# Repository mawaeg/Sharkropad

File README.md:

# Sharkropad

**Sharkropad** is an open-source hotswappable macropad supporting QMK/VIA.

This repository includes a custom pcb design, a 3d printed case and QMK/VIA firmware.

## Features
- **USB-C with ESD Protection**
- **Rotary Encoder**
- **OLED Display**
- **Customizable RGB Lighting**
- **Customizable keymap using VIA**
- **Hot-Swappable Switches**
- **Powered by a STM32L432 MCU**

## Getting Started

### Pcb

The Sharkropad is based on a custom pcb. You can find the manufacturing files in the latest release.

I got my pcb manufactured and assembled from [JLCPCB](https://jlcpcb.com/).

In case you want to assemble the pcb yourself you can find all the needed parts in the bom in the latest release.

### Other needed parts

| Part                      | Quantity  | Link (recommendation) | Note |
|---------------------------|-----------|-----------------------|------|
| filament of your choice   | 50g       | [3djake.de](https://www.3djake.de/polymaker/polyterra-pla-charcoal-black)                   | For the top parts (I used a matte black PLA filament)
| transparent filament      | 30g       | [redline-filament.com](https://redline-filament.com/collections/pla-filament/products/premium-pla-transparent?variant=50149105041672)                  | Transparent bottom parts for the underglow
| M2.5 Heat Inserts         | 4         | [cnckitchen.store](https://cnckitchen.store/products/gewindeeinsatz-threaded-insert-m2-5-standard-100-stk-pcs)                   |
| M2.5 x 12 Screws          | 4         | [cnckitchen.store](https://cnckitchen.store/products/m2-5-screw-stainless-steel-aisi-304-low-head?variant=47945362833743)                  |
| Protective buffer         | 4         | [amazon.de](https://www.amazon.de/dp/B01N0X4Y38?ref=ppx_yo2ov_dt_b_fed_asin_title&th=1) |
| Keycaps                   | 12        | [aliexpress.com](https://de.aliexpress.com/item/1005006660909685.html?spm=a2g0o.order_list.order_list_main.15.49fc5c5fYY4A21&gatewayAdapt=glo2deu)
| Stranded wire             | 10cm      | tbd | Currently there is a problem with the pcb when using the underglow leds where a cable needs to be soldered
| Rotary Encoder            | 1         | [42keebs.eu](https://42keebs.eu/shop/parts/ec11-rotary-encoder/?attribute_type=Bourns%20(larger%20body)) | This particular one works with the case and the knob
| OLED display              | 1         | [42keebs.eu](https://42keebs.eu/shop/parts/oled-display-0-91-128x32/?attribute_pcb-colour=Black)
| OLED socket (low profile) | 1         | [42keebs.eu](https://42keebs.eu/shop/parts/low-profile-oled-sockets/) 
| Hotswap sockets           | 12        | [42keebs.eu](https://42keebs.eu/shop/parts/kailh-mx-hot-swap-sockets/) | (2 x 10 sockets) !Cherry MX-style!
| Switches                  | 12        | [candykeys.com](https://candykeys.com/product/hmx-silent-sakura) | Any MX compatible switch is fine

### 3d printed case

The case consists of 4 3d printed parts:
- Bottom part of the case
- Top part of the case
- Plate for the switches
- Rotary encoder knob

The stl files for the 3d printed parts can be found under [cad/stl/](cad/stl/).

The parts are created with [OpenSCAD](https://openscad.org/) and the source code is stored at [cad/](cad/).

#### Print settings

For the bottom part of the case I used transparent PLA to make the underglow leds shine through.

For the top part of the case, the plate and the rotary encoder knob I used matte black PLA.

I printed the case and the plate with default print settings with a layer height of .2mm.

> **_NOTE:_** For the top and bottom case you will need some supports for the cutouts for the encoder and the screw heads. Default support settings should work just fine. (I like to use organic supports.)

The rotary encoder knob should be printed with a layer height of .2mm and at least 3 solid bottom layers.

### Building the Sharkropad

1. Get a PCB and prepare it by soldering the components onto it (if not already done through SMT assembly)
2. Assemble the rotary encoder, the oled socket and the hotswap sockets (if not already done)
3. Fix the issue with the pcb as shown in [this chapter](#fixing-the-pcb)

    <div style="display: flex;">

    </div>

4. Place a foam (as shown) to support the OLED and mount the oled:

5. Assemble the switches (put the plate between pcb and switches) and the keycaps
6. Insert the heat inserts into the holes provided in the top part:

7. Put the protective buffers on the bottom case to prevent the macropad from sliding around:

8. Screw the case together with the pcb in between and put the knob on the rotary encoder

### Flashing the firmware

> **_NOTE:_** Once the firmware is flashed once you can enter bootloader mode by disconnecting the macropad, pressing and holding the encoder knob while plugging it back in. Then the macropad is in bootloader mode and you can connect to it  and program it using the CubeProgrammer or flash using QMK.

1. Get the provided firmware in the latest release
    - If you want to be able to use VIA to modify the keymap you should use `sharkropad_via.bin`
    - If you only need QMK functionality you can also use ` sharkropad_default.bin`
    
2. Flash the firmware using the [STM32 CubeProgrammer](https://www.st.com/en/development-tools/stm32cubeprog.html) as shown below:

#### Flash using QMK

As the firmware is not currently in the qmk github repository flashing with QMK is more complicated.
- You need to setup your QMK Environment
- Copy the firmware into the QMK folder:
    - Copy the contents of the firmware folder to a folder named `sharkropad` under `qmk_firmware/keyboards`
    - Target structure: `qmk_firmware/keyboards/sharkropad`:

- You can then compile and flash using qmk:
    ```shell
    qmk compile -kb sharkropad -km default
    qmk flash -kb sharkropad -km default
    ```

    or for via compatible firmware:
    ```shell
    qmk compile -kb sharkropad -km via
    qmk flash -kb sharkropad -km via
    ```

### Fixing the pcb

In the current design of the pcb, the rgb underglow and the rgb matrix for the keys are connected to different Output pins of the STM32.
However that is not supported by QMK. Therefore a cable needs to be manually soldered to also make the rgb underglow working:
- Remove the resistor R10
- Solder a cable from the left contact of R10 to the bottom contact of R13

## Customize the keymap using VIA

VIA is a tool that allows you to customize the keymap of your keyboard.

As the configuration for this macropad is not yet added to the via repository a manual step is needed to customize using VIA.

1. Open the VIA web app at [https://usevia.app/](https://usevia.app/)
2. Navigate to the settings and ensure the `Show Design tab` option is enabled

3. Open the design tab and press `Load` (Draft Definition)

4. Select the `via.json` provided in this release. You should now see a model of the macropad:

5. You can now open the Customize window where you need to click `Authorize device +`

6. Select the device with Sharkropad in its name

You can now customize the individual keys and also customize the RGB Lighting:

## License

This project is licensed under the GNU General Public License v3.0. See the [LICENSE](LICENSE) file for details.

This project includes third-party components (libraries and fonts) that are licensed under their respective terms. These components are not covered by the GPLv3 license of this project. Users must adhere to the specific licenses provided in the respective directories.

### Libraries used for the pcb

For the creation of the pcb various libraries where used. 

A copy of most of them are included in this project to make the kicad project work without manually installing those libraries. 

Those libraries are stored under [/electronics/lib/](/electronics/lib/).

The libraries are licensed under their respective license. Please be aware of the `README.md` and `LICENSE.md` files in the lib folder.

### Font used on the pcb

The font used under the logo on the pcb is [Cherry Bomb One](https://github.com/satsuyako/CherryBomb).

A copy of the font is kept under [_assets/Cherry_Bomb_One](_assets/Cherry_Bomb_One). 
To make the font display correctly in KiCad you need to install it on your OS.

This font itself is licensed under the original OFL-1.1 License.
Please be aware of the License: [OFL.txt](_assets/Cherry_Bomb_One/OFL.txt)

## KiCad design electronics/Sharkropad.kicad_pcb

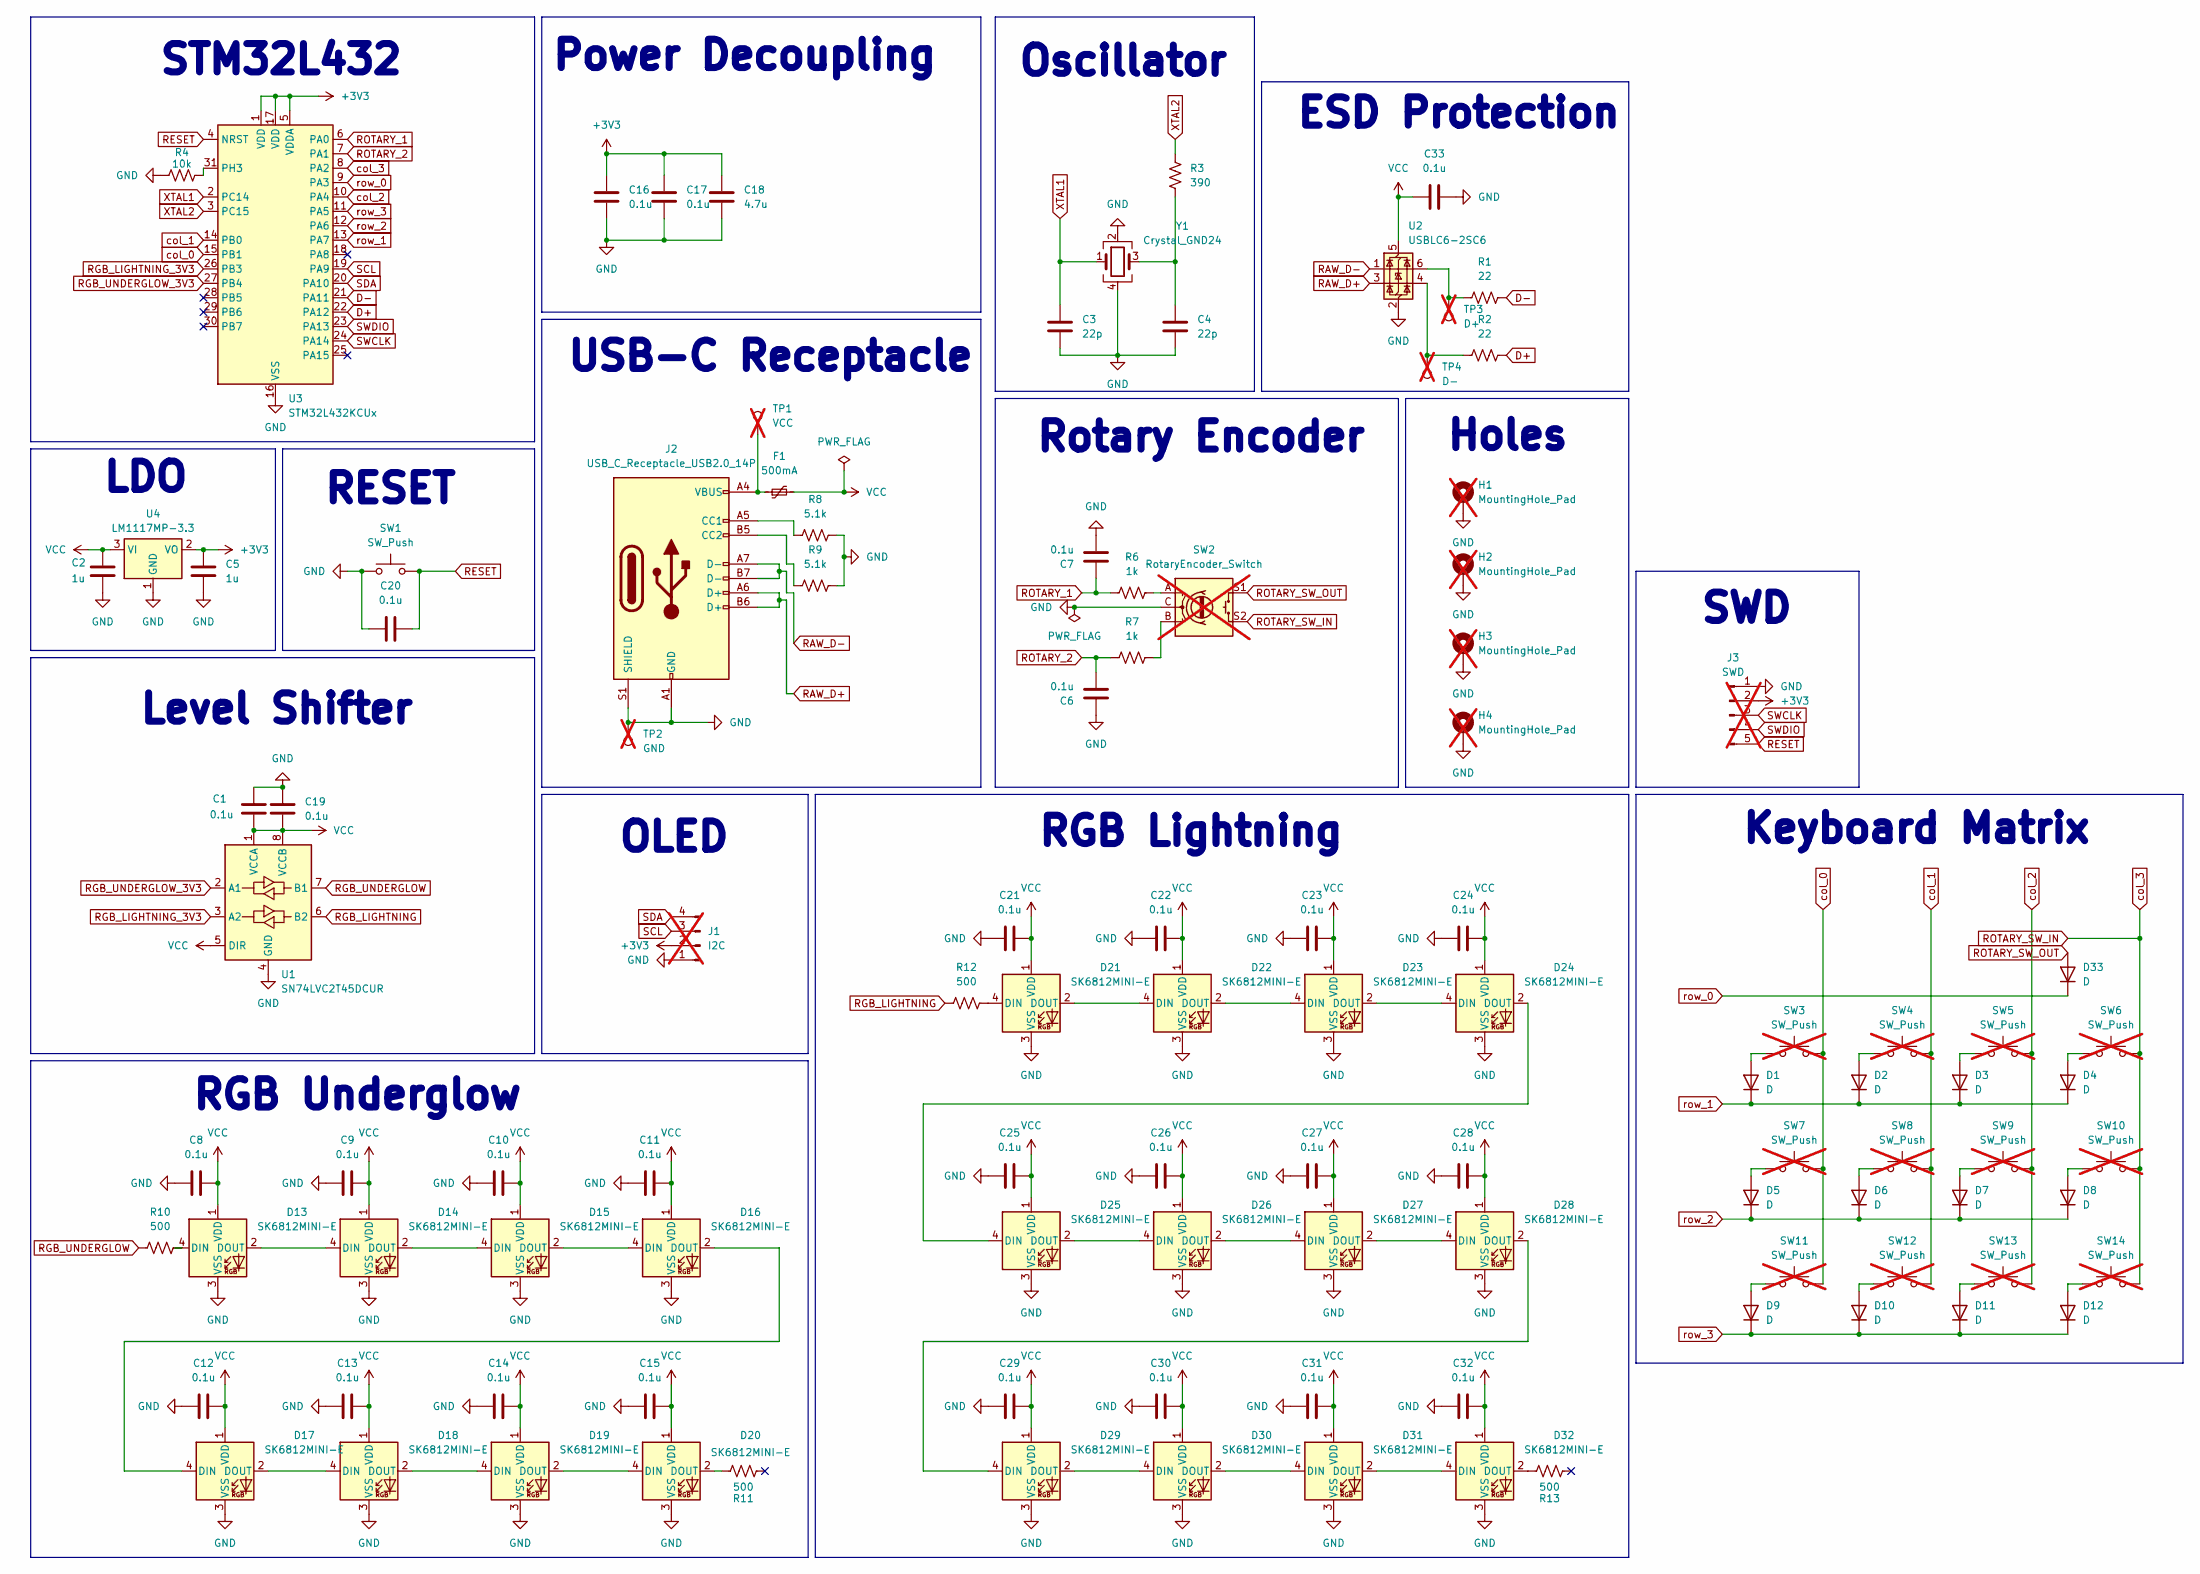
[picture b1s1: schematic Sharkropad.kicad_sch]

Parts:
C1, C6, C7, C8, C9, C10, C11, C12, C13, C14, C15, C16, C17, C19, C20, C21, C22, C23, C24, C25, C26, C27, C28, C29, C30, C31, C32, C33: 0.1u; C_0603_1608Metric; MPN GCM188R71C104KA37J
C2, C5: 1u; C_0603_1608Metric; MPN GRM188C81E105KAADD
C3, C4: 22p; C_0603_1608Metric; MPN GRM1885C2A220JA01J
C18: 4.7u; C_0603_1608Metric; MPN GCJ188C70J475KE02D
D1, D2, D3, D4, D5, D6, D7, D8, D9, D10, D11, D12, D33: D; D_SOD-123F; MPN BAS16H,115
D13, D14, D15, D16, D17, D18, D19, D20, D21, D22, D23, D24, D25, D26, D27, D28, D29, D30, D31, D32: SK6812MINI-E; SK6812-MINI-E; MPN SK6812MINI-E
F1: 500mA; Fuse_0603_1608Metric; MPN MF-FSML050/8-2
H1, H2, H3, H4: MountingHole_Pad; MountingHole_2.5mm_Pad; not fitted
J1: I2C; PinHeader_1x04_P2.54mm_Vertical; not fitted
J2: USB_C_Receptacle_USB2.0_14P; USB_C_Receptacle_GCT_USB4105-xx-A_16P_TopMnt_Horizontal; MPN USB4105-GF-A-120
J3: SWD; PinHeader_1x05_P2.54mm_Vertical; not fitted
R1, R2: 22; R_0603_1608Metric; MPN CRCW060322R0FKEA
R3: 390; R_0603_1608Metric; MPN CRCW0603390RFKEA
R4: 10k; R_0603_1608Metric; MPN CRCW060310K0FKEI
R6, R7: 1k; R_0603_1608Metric; MPN CRCW06031K00FKED
R8, R9: 5.1k; R_0603_1608Metric; MPN CRCW06035K10FKEC
R10, R11, R12, R13: 500; R_0603_1608Metric; MPN CRCW0603499RFKEA
SW1: SW_Push; SW_SPST_TL3342; MPN TL3342F160QG
SW2: RotaryEncoder_Switch; RotaryEncoder_Alps_EC11E-Switch_Vertical_H20mm; not fitted
SW3, SW4, SW5, SW6, SW7, SW8, SW9, SW10, SW11, SW12, SW13, SW14: SW_Push; SW_Hotswap_Kailh_MX_1.00u; not fitted
TP1: VCC; TestPoint_Pad_D1.0mm; not fitted
TP2: GND; TestPoint_Pad_D1.0mm; not fitted
TP3: D+; TestPoint_Pad_D1.0mm; not fitted
TP4: D-; TestPoint_Pad_D1.0mm; not fitted
U1: SN74LVC2T45DCUR; VSSOP-8_2.3x2mm_P0.5mm; MPN SN74LVC2T45DCURE4
U2: USBLC6-2SC6; SOT-23-6; MPN USBLC6-2SC6
U3: STM32L432KCUx; QFN-32-1EP_5x5mm_P0.5mm_EP3.45x3.45mm; MPN STM32L432KCU6
U4: LM1117MP-3.3; SOT-223-3_TabPin2; MPN LM1117MPX-3.3/NOPB
Y1: Crystal_GND24; Crystal_SMD_SeikoEpson_FA238-4Pin_3.2x2.5mm; MPN ECS-80-18-33-JGN-TR

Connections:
+3V3: C5.1, C16.1, C17.1, C18.1, J1.2, J3.2, U3.1 (VDD), U3.5 (VDDA), U3.17 (VDD), U4.2 (VO)
D+: R2.1, U3.22 (PA12)
D-: R1.1, U3.21 (PA11)
GND: C1.1, C2.2, C3.2, C4.2, C5.2, C6.1, C7.2, C8.1, C9.1, C10.1, C11.1, C12.1, C13.1, C14.1, C15.1, C16.2, C17.2, C18.2, C19.1, C20.2, C21.1, C22.1, C23.1, C24.1, C25.1, C26.1, C27.1, C28.1, C29.1, C30.1, C31.1, C32.1, C33.2, D13.3 (VSS), D14.3 (VSS), D15.3 (VSS), D16.3 (VSS), D17.3 (VSS), D18.3 (VSS), D19.3 (VSS), D20.3 (VSS), D21.3 (VSS), D22.3 (VSS), D23.3 (VSS), D24.3 (VSS), D25.3 (VSS), D26.3 (VSS), D27.3 (VSS), D28.3 (VSS), D29.3 (VSS), D30.3 (VSS), D31.3 (VSS), D32.3 (VSS), H1.1, H2.1, H3.1, H4.1, J1.1, J2.A1 (GND), J2.A12 (GND), J2.B1 (GND), J2.B12 (GND), J2.S1 (SHIELD), J3.1, R4.2, R8.2, R9.2, SW1.1, SW2.C, TP2.1, U1.4 (GND), U2.2 (GND), U3.16 (VSS), U3.32 (VSS), U3.33 (VSS), U4.1 (GND), Y1.2, Y1.4
unnamed: C4.1, R3.2, Y1.3
unnamed: D1.2 (A), SW3.1
unnamed: D2.2 (A), SW4.1
unnamed: D3.2 (A), SW5.1
unnamed: D4.2 (A), SW6.1
unnamed: D5.2 (A), SW7.1
unnamed: D6.2 (A), SW8.1
unnamed: D7.2 (A), SW9.1
unnamed: D8.2 (A), SW10.1
unnamed: D9.2 (A), SW11.1
unnamed: D10.2 (A), SW12.1
unnamed: D11.2 (A), SW13.1
unnamed: D12.2 (A), SW14.1
unnamed: D13.4 (DIN), R10.2
unnamed: D13.2 (DOUT), D14.4 (DIN)
unnamed: D14.2 (DOUT), D15.4 (DIN)
unnamed: D15.2 (DOUT), D16.4 (DIN)
unnamed: D16.2 (DOUT), D17.4 (DIN)
unnamed: D17.2 (DOUT), D18.4 (DIN)
unnamed: D18.2 (DOUT), D19.4 (DIN)
unnamed: D19.2 (DOUT), D20.4 (DIN)
unnamed: D20.2 (DOUT), R11.1
unnamed: D21.4 (DIN), R12.2
unnamed: D21.2 (DOUT), D22.4 (DIN)
unnamed: D22.2 (DOUT), D23.4 (DIN)
unnamed: D23.2 (DOUT), D24.4 (DIN)
unnamed: D24.2 (DOUT), D25.4 (DIN)
unnamed: D25.2 (DOUT), D26.4 (DIN)
unnamed: D26.2 (DOUT), D27.4 (DIN)
unnamed: D27.2 (DOUT), D28.4 (DIN)
unnamed: D28.2 (DOUT), D29.4 (DIN)
unnamed: D29.2 (DOUT), D30.4 (DIN)
unnamed: D30.2 (DOUT), D31.4 (DIN)
unnamed: D31.2 (DOUT), D32.4 (DIN)
unnamed: D32.2 (DOUT), R13.1
unnamed: F1.1, J2.A4 (VBUS), J2.A9 (VBUS), J2.B4 (VBUS), J2.B9 (VBUS), TP1.1
unnamed: J2.A5 (CC1), R8.1
unnamed: J2.B5 (CC2), R9.1
unnamed: R1.2, TP3.1, U2.6 (I/O1)
unnamed: R2.2, TP4.1, U2.4 (I/O2)
unnamed: R6.2, SW2.A
unnamed: R7.2, SW2.B
unnamed: R4.1, U3.31 (PH3)
RAW_D+: J2.A6 (D+), J2.B6 (D+), U2.3 (I/O2)
RAW_D-: J2.A7 (D-), J2.B7 (D-), U2.1 (I/O1)
RESET: C20.1, J3.5, SW1.2, U3.4 (NRST)
RGB_LIGHTNING: R12.1, U1.6 (B2)
RGB_LIGHTNING_3V3: U1.3 (A2), U3.26 (PB3)
RGB_UNDERGLOW: R10.1, U1.7 (B1)
RGB_UNDERGLOW_3V3: U1.2 (A1), U3.27 (PB4)
ROTARY_1: C7.1, R6.1, U3.6 (PA0)
ROTARY_2: C6.2, R7.1, U3.7 (PA1)
ROTARY_SW_IN: SW2.S2, SW6.2, SW10.2, SW14.2, U3.8 (PA2)
ROTARY_SW_OUT: D33.2 (A), SW2.S1
SCL: J1.3, U3.19 (PA9)
SDA: J1.4, U3.20 (PA10)
SWCLK: J3.3, U3.24 (PA14)
SWDIO: J3.4, U3.23 (PA13)
VCC: C1.2, C2.1, C8.2, C9.2, C10.2, C11.2, C12.2, C13.2, C14.2, C15.2, C19.2, C21.2, C22.2, C23.2, C24.2, C25.2, C26.2, C27.2, C28.2, C29.2, C30.2, C31.2, C32.2, C33.1, D13.1 (VDD), D14.1 (VDD), D15.1 (VDD), D16.1 (VDD), D17.1 (VDD), D18.1 (VDD), D19.1 (VDD), D20.1 (VDD), D21.1 (VDD), D22.1 (VDD), D23.1 (VDD), D24.1 (VDD), D25.1 (VDD), D26.1 (VDD), D27.1 (VDD), D28.1 (VDD), D29.1 (VDD), D30.1 (VDD), D31.1 (VDD), D32.1 (VDD), F1.2, U1.1 (VCCA), U1.5 (DIR), U1.8 (VCCB), U2.5 (VBUS), U4.3 (VI)
XTAL1: C3.1, U3.2 (PC14), Y1.1
XTAL2: R3.1, U3.3 (PC15)
col_0: SW3.2, SW7.2, SW11.2, U3.15 (PB1)
col_1: SW4.2, SW8.2, SW12.2, U3.14 (PB0)
col_2: SW5.2, SW9.2, SW13.2, U3.10 (PA4)
row_0: D33.1 (K), U3.9 (PA3)
row_1: D1.1 (K), D2.1 (K), D3.1 (K), D4.1 (K), U3.13 (PA7)
row_2: D5.1 (K), D6.1 (K), D7.1 (K), D8.1 (K), U3.12 (PA6)
row_3: D9.1 (K), D10.1 (K), D11.1 (K), D12.1 (K), U3.11 (PA5)

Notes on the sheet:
STM32L432
LDO
USB-C Receptacle
ESD Protection
Holes
SWD
Level Shifter
Power Decoupling
Oscillator
RGB Underglow
Keyboard Matrix
RESET
RGB Lightning
OLED
Rotary Encoder

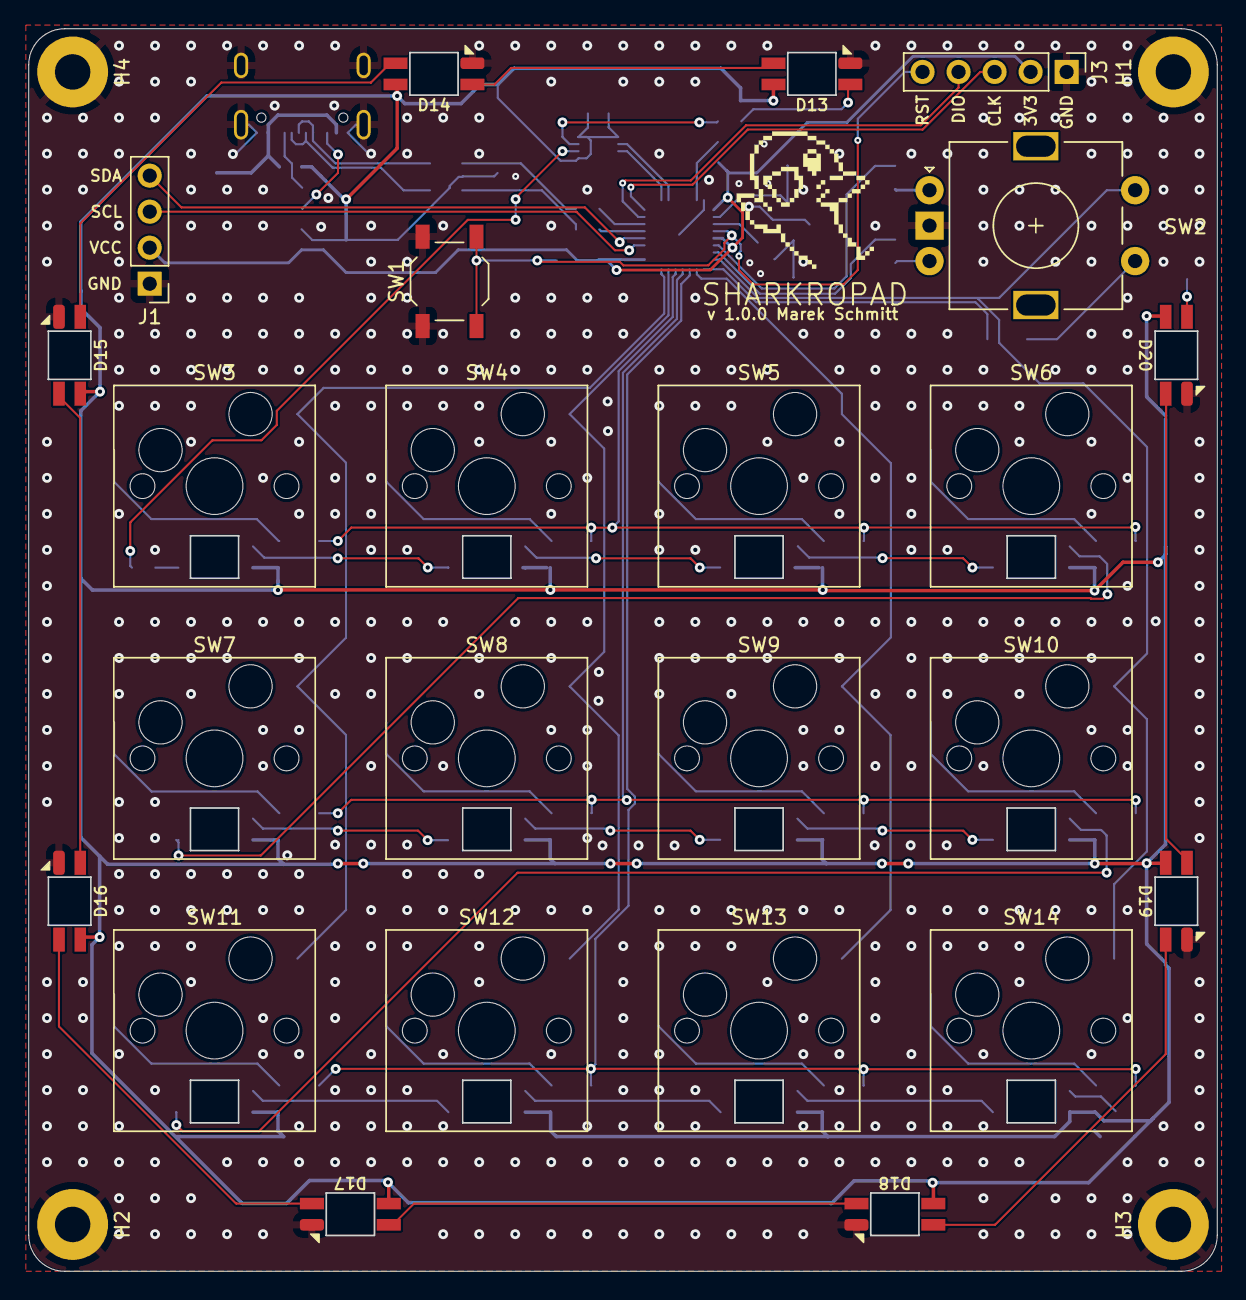
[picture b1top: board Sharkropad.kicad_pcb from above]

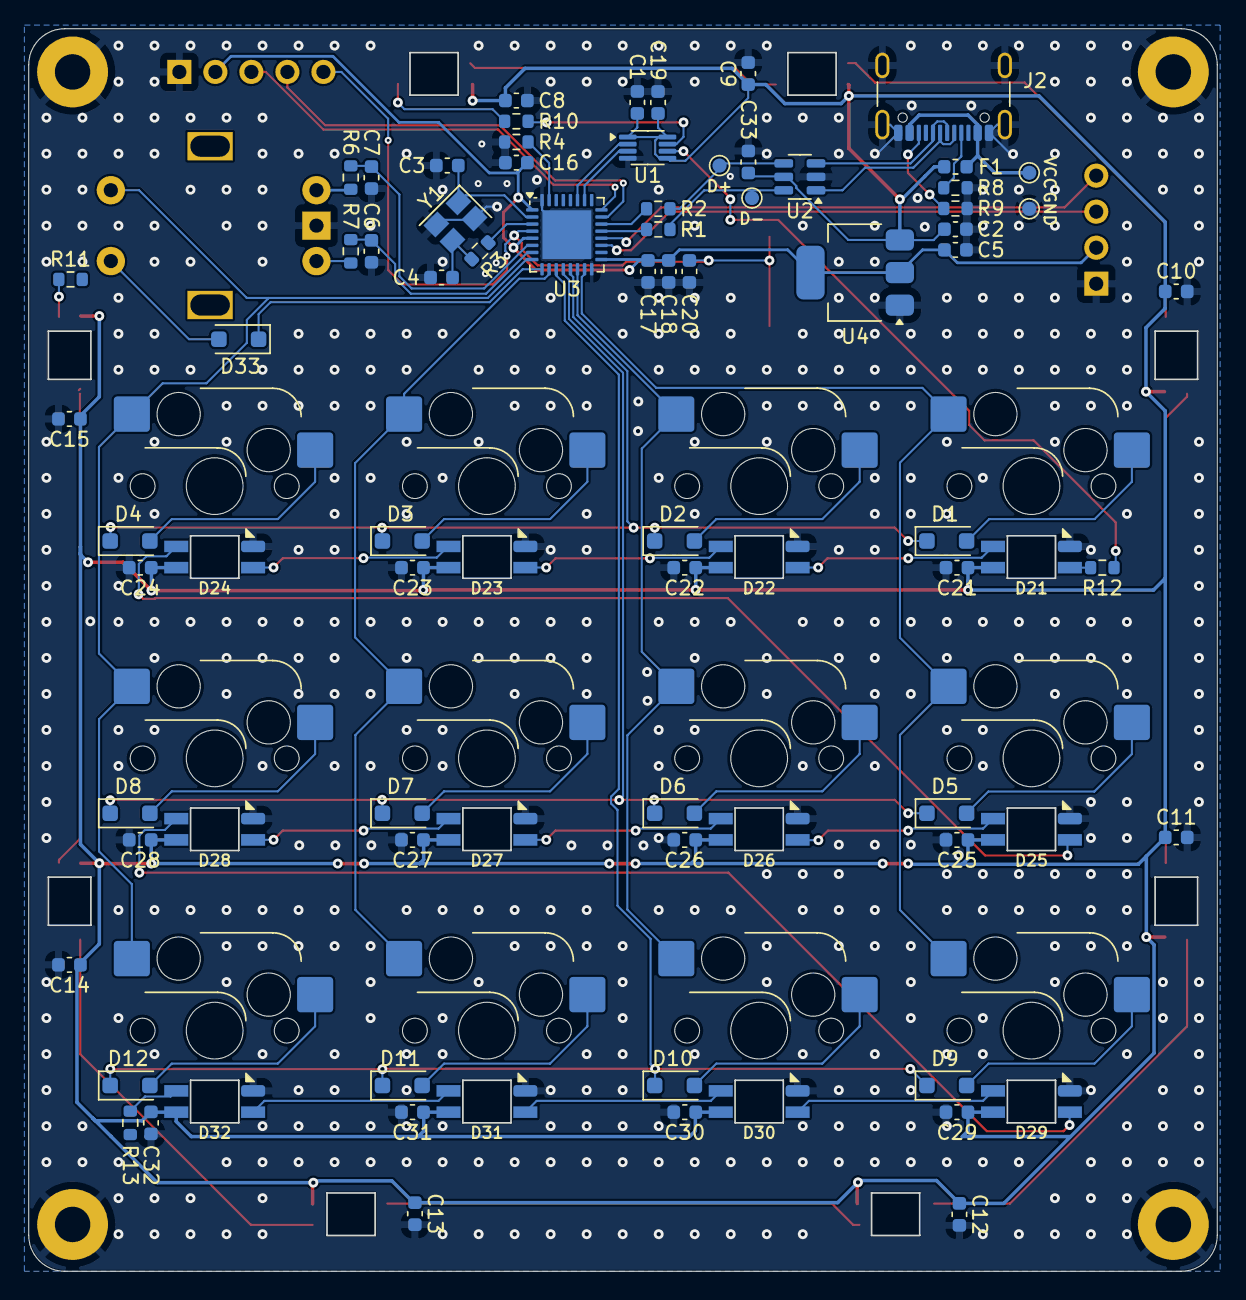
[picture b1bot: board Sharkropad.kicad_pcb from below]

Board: 2 copper layers, 83.8 x 87.6 mm, 109 parts (81 on the bottom side), 72 nets.

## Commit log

2025-02-04 Improve readme
2025-02-07 Add scad based knob
2025-02-10 Add missing cutouts for encoder and oled
2025-02-16 Improve print settings chapter
2025-02-17 [firmware] Fix syntax error
2025-02-19 [firmware] Add support for via
2025-02-25 [docs] Add information for via support to readme
2025-02-27 [firmware] Migrate to data-driven approach
2025-03-27 Fix link to wrong hotswap sockets
2025-04-14 [firmware] Various improvements
    Use PWM driver instead of bitbanging for rgb lighting
    Move oled task to sharkropad file and improve effect handling with automatic effect list generation and automatic scrolling for effect names that don't fit a single line
2025-05-13 Add switches to needed parts
